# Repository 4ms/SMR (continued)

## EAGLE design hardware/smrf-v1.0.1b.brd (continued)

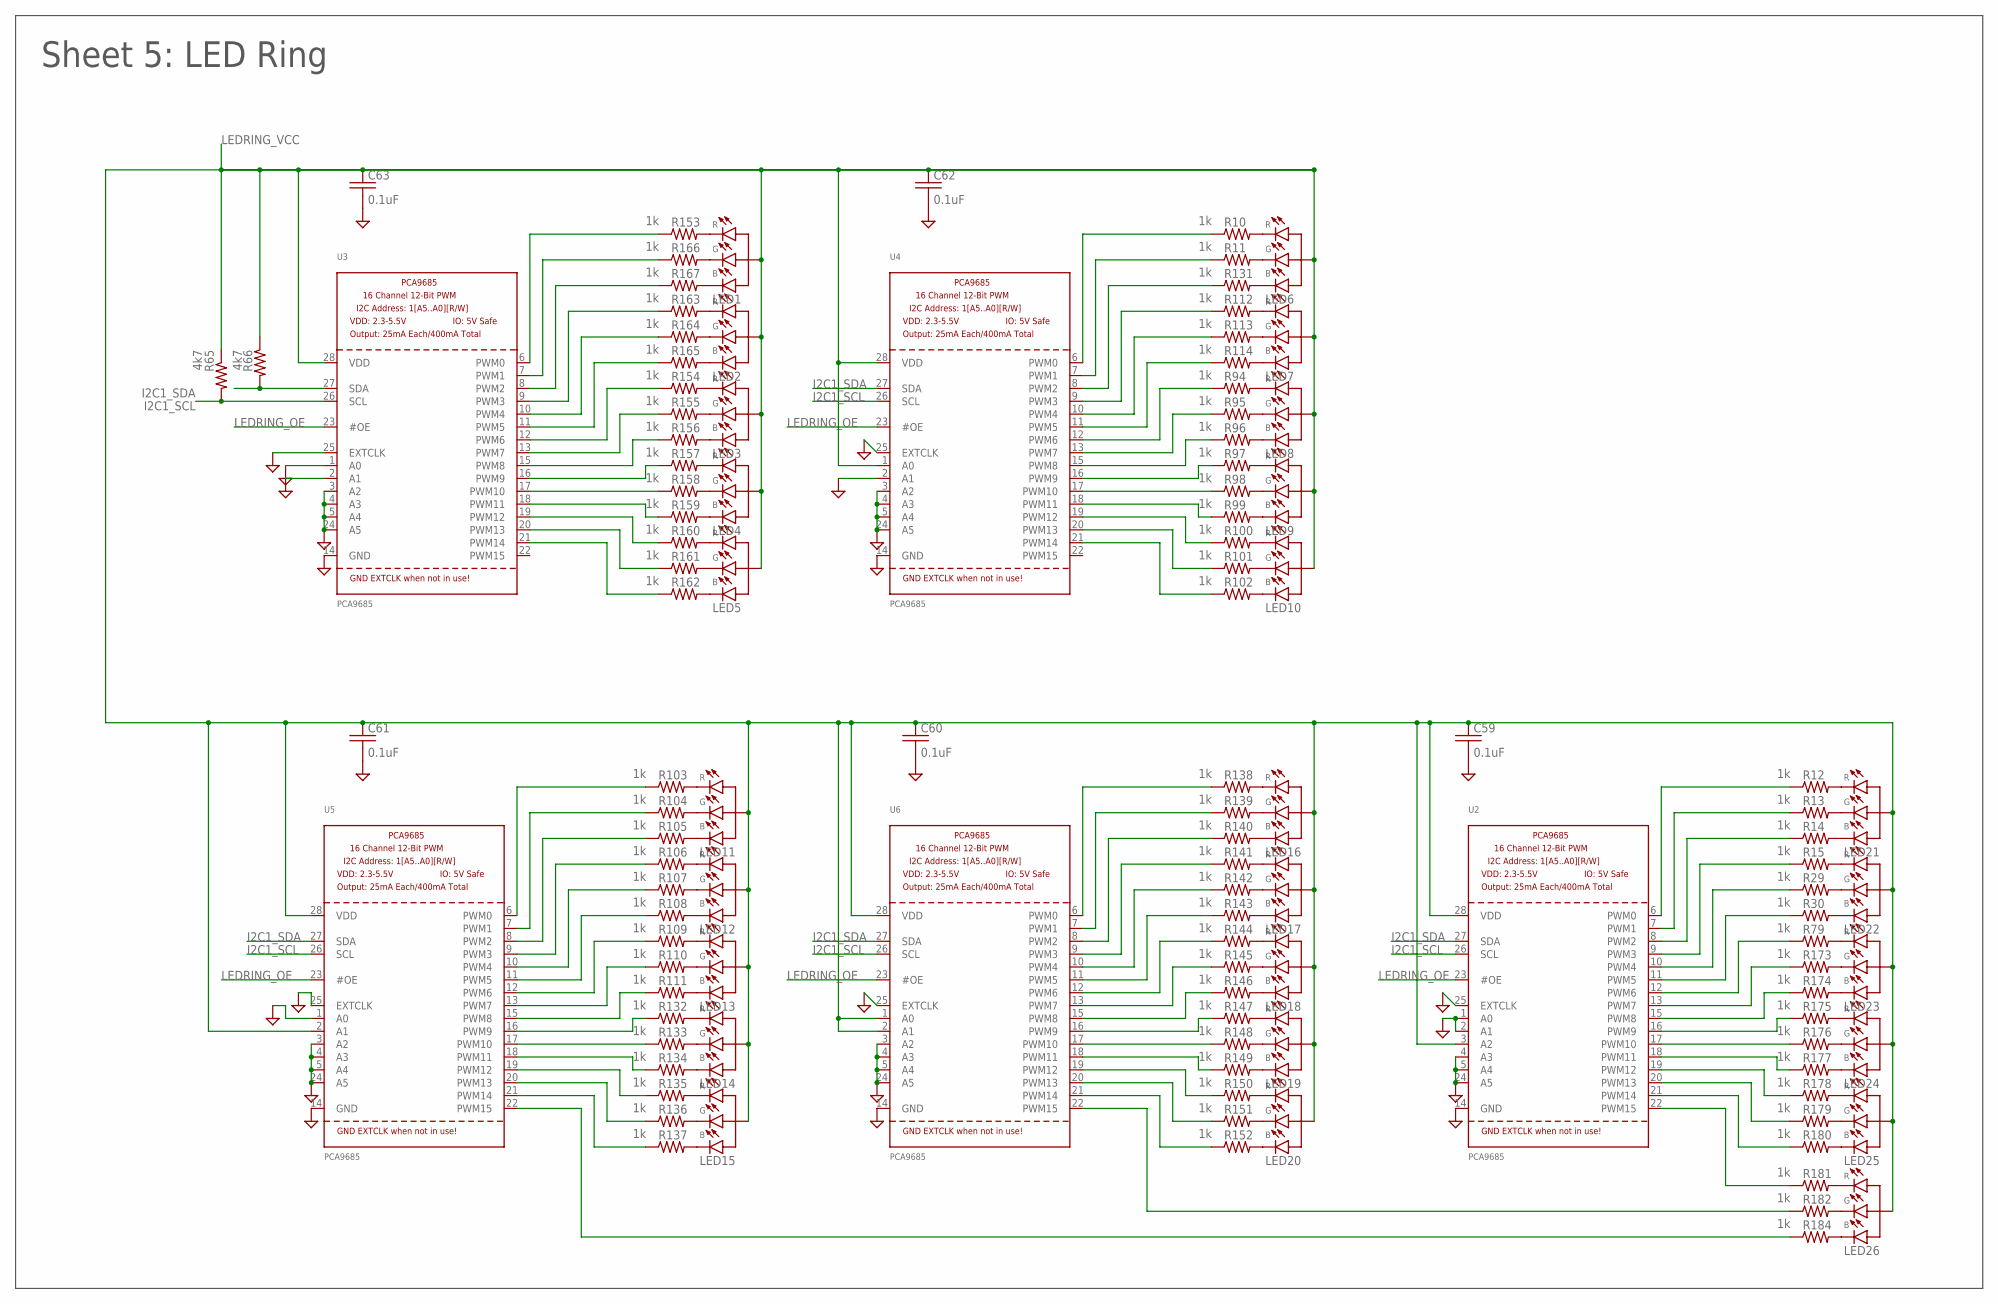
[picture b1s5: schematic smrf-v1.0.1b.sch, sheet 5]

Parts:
C59, C60, C61, C62, C63: 0.1uF; C0603
LED1, LED2, LED3, LED4, LED5, LED6, LED7, LED8, LED9, LED10, LED11, LED12, LED13, LED14, LED15, LED16, LED17, LED18, LED19, LED20, LED21, LED22, LED23, LED24, LED25, LED26: LED-RGB-CA-HEBEI; PLCC4
R10, R11, R12, R13, R14, R15, R29, R30, R79, R94, R95, R96, R97, R98, R99, R100, R101, R102, R103, R104, R105, R106, R107, R108, R109, R110, R111, R112, R113, R114, R131, R132, R133, R134, R135, R136, R137, R138, R139, R140, R141, R142, R143, R144, R145, R146, R147, R148, R149, R150, R151, R152, R153, R154, R155, R156, R157, R158, R159, R160, R161, R162, R163, R164, R165, R166, R167, R173, R174, R175, R176, R177, R178, R179, R180, R181, R182, R184: 1k; R0603
R65, R66: 4k7; R0603
U2, U3, U4, U5, U6: PCA9685; TSSOP28

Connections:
GND: C59.2, C60.2, C61.2, C62.2, C63.2, U2.1 (A0), U2.2 (A1), U2.4 (A3), U2.5 (A4), U2.14 (GND), U2.24 (A5), U2.25 (EXTCLK), U3.1 (A0), U3.2 (A1), U3.3 (A2), U3.4 (A3), U3.5 (A4), U3.14 (GND), U3.24 (A5), U3.25 (EXTCLK), U4.2 (A1), U4.3 (A2), U4.4 (A3), U4.5 (A4), U4.14 (GND), U4.24 (A5), U4.25 (EXTCLK), U5.1 (A0), U5.3 (A2), U5.4 (A3), U5.5 (A4), U5.14 (GND), U5.24 (A5), U5.25 (EXTCLK), U6.3 (A2), U6.4 (A3), U6.5 (A4), U6.14 (GND), U6.24 (A5), U6.25 (EXTCLK); also elsewhere on the board
I2C1_SCL: R65.2, U2.26 (SCL), U3.26 (SCL), U4.26 (SCL), U5.26 (SCL), U6.26 (SCL); also elsewhere on the board
I2C1_SDA: R66.2, U2.27 (SDA), U3.27 (SDA), U4.27 (SDA), U5.27 (SDA), U6.27 (SDA); also elsewhere on the board
LEDRING_OE: U2.23 (#OE), U3.23 (#OE), U4.23 (#OE), U5.23 (#OE), U6.23 (#OE); also elsewhere on the board
LEDRING_VCC: C59.1, C60.1, C61.1, C62.1, C63.1, LED1.P$2 (A), LED2.P$2 (A), LED3.P$2 (A), LED4.P$2 (A), LED5.P$2 (A), LED6.P$2 (A), LED7.P$2 (A), LED8.P$2 (A), LED9.P$2 (A), LED10.P$2 (A), LED11.P$2 (A), LED12.P$2 (A), LED13.P$2 (A), LED14.P$2 (A), LED15.P$2 (A), LED16.P$2 (A), LED17.P$2 (A), LED18.P$2 (A), LED19.P$2 (A), LED20.P$2 (A), LED21.P$2 (A), LED22.P$2 (A), LED23.P$2 (A), LED24.P$2 (A), LED25.P$2 (A), LED26.P$2 (A), R65.1, R66.1, U2.3 (A2), U2.28 (VDD), U3.28 (VDD), U4.1 (A0), U4.28 (VDD), U5.2 (A1), U5.28 (VDD), U6.1 (A0), U6.2 (A1), U6.28 (VDD); also elsewhere on the board
unnamed: LED1.P$1 (CR), R153.2
unnamed: LED1.P$4 (CG), R166.2
unnamed: R12.1, U2.6 (PWM0)
unnamed: R13.1, U2.7 (PWM1)
unnamed: R14.1, U2.8 (PWM2)
unnamed: R15.1, U2.9 (PWM3)
unnamed: LED1.P$3 (CB), R167.2
unnamed: R29.1, U2.10 (PWM4)
unnamed: R30.1, U2.11 (PWM5)
unnamed: LED2.P$1 (CR), R163.2
unnamed: LED2.P$4 (CG), R164.2
unnamed: LED2.P$3 (CB), R165.2
unnamed: LED3.P$1 (CR), R154.2
unnamed: LED3.P$4 (CG), R155.2
unnamed: LED3.P$3 (CB), R156.2
unnamed: LED4.P$1 (CR), R157.2
unnamed: LED4.P$4 (CG), R158.2
unnamed: LED4.P$3 (CB), R159.2
unnamed: R79.1, U2.12 (PWM6)
unnamed: R173.1, U2.13 (PWM7)
unnamed: R174.1, U2.15 (PWM8)
unnamed: LED5.P$1 (CR), R160.2
unnamed: LED5.P$4 (CG), R161.2
unnamed: LED5.P$3 (CB), R162.2
unnamed: LED6.P$1 (CR), R10.2
unnamed: LED6.P$4 (CG), R11.2
unnamed: LED6.P$3 (CB), R131.2
unnamed: LED7.P$1 (CR), R112.2
unnamed: LED7.P$4 (CG), R113.2
unnamed: LED7.P$3 (CB), R114.2
unnamed: LED8.P$1 (CR), R94.2
unnamed: LED8.P$4 (CG), R95.2
unnamed: LED8.P$3 (CB), R96.2
unnamed: LED9.P$1 (CR), R97.2
unnamed: LED9.P$4 (CG), R98.2
unnamed: LED9.P$3 (CB), R99.2
unnamed: LED10.P$1 (CR), R100.2
unnamed: LED10.P$4 (CG), R101.2
unnamed: LED10.P$3 (CB), R102.2
unnamed: LED11.P$1 (CR), R103.2
unnamed: R175.1, U2.16 (PWM9)
unnamed: LED11.P$4 (CG), R104.2
unnamed: LED11.P$3 (CB), R105.2
unnamed: LED12.P$1 (CR), R106.2
unnamed: LED12.P$4 (CG), R107.2
unnamed: LED12.P$3 (CB), R108.2
unnamed: LED13.P$1 (CR), R109.2
unnamed: LED13.P$4 (CG), R110.2
unnamed: LED14.P$1 (CR), R132.2
unnamed: LED14.P$4 (CG), R133.2
unnamed: LED14.P$3 (CB), R134.2
unnamed: LED15.P$1 (CR), R135.2
unnamed: LED15.P$4 (CG), R136.2
unnamed: R176.1, U2.17 (PWM10)
unnamed: R177.1, U2.18 (PWM11)
unnamed: LED15.P$3 (CB), R137.2
unnamed: LED16.P$1 (CR), R138.2
unnamed: LED16.P$4 (CG), R139.2
unnamed: LED16.P$3 (CB), R140.2
unnamed: LED17.P$1 (CR), R141.2
unnamed: LED17.P$4 (CG), R142.2
unnamed: LED17.P$3 (CB), R143.2
unnamed: LED18.P$1 (CR), R144.2
unnamed: LED18.P$4 (CG), R145.2
unnamed: LED18.P$3 (CB), R146.2
unnamed: LED19.P$1 (CR), R147.2
unnamed: LED19.P$4 (CG), R148.2
unnamed: LED19.P$3 (CB), R149.2
unnamed: LED20.P$1 (CR), R150.2
unnamed: LED20.P$4 (CG), R151.2
unnamed: LED20.P$3 (CB), R152.2
unnamed: LED13.P$3 (CB), R111.2
unnamed: R153.1, U3.6 (PWM0)
unnamed: R166.1, U3.7 (PWM1)
unnamed: R167.1, U3.8 (PWM2)
unnamed: R163.1, U3.9 (PWM3)
unnamed: R164.1, U3.10 (PWM4)
unnamed: R165.1, U3.11 (PWM5)
unnamed: R154.1, U3.12 (PWM6)
unnamed: R155.1, U3.13 (PWM7)
unnamed: R156.1, U3.15 (PWM8)
unnamed: R157.1, U3.16 (PWM9)
unnamed: R158.1, U3.17 (PWM10)
unnamed: R159.1, U3.18 (PWM11)
unnamed: R160.1, U3.19 (PWM12)
unnamed: R161.1, U3.20 (PWM13)
unnamed: R162.1, U3.21 (PWM14)
unnamed: R178.1, U2.19 (PWM12)
unnamed: R10.1, U4.6 (PWM0)
unnamed: R11.1, U4.7 (PWM1)
unnamed: R131.1, U4.8 (PWM2)
unnamed: R112.1, U4.9 (PWM3)
unnamed: R113.1, U4.10 (PWM4)
unnamed: R114.1, U4.11 (PWM5)
unnamed: R94.1, U4.12 (PWM6)
unnamed: R95.1, U4.13 (PWM7)
unnamed: R96.1, U4.15 (PWM8)
unnamed: R97.1, U4.16 (PWM9)
unnamed: R98.1, U4.17 (PWM10)
unnamed: R99.1, U4.18 (PWM11)
unnamed: R100.1, U4.19 (PWM12)
unnamed: R101.1, U4.20 (PWM13)
unnamed: R102.1, U4.21 (PWM14)
unnamed: R179.1, U2.20 (PWM13)
unnamed: R103.1, U5.6 (PWM0)
unnamed: R104.1, U5.7 (PWM1)
unnamed: R105.1, U5.8 (PWM2)
unnamed: R106.1, U5.9 (PWM3)
unnamed: R107.1, U5.10 (PWM4)
unnamed: R108.1, U5.11 (PWM5)
unnamed: R109.1, U5.12 (PWM6)
unnamed: R110.1, U5.13 (PWM7)
unnamed: R111.1, U5.15 (PWM8)
unnamed: R132.1, U5.16 (PWM9)
unnamed: R133.1, U5.17 (PWM10)
unnamed: R134.1, U5.18 (PWM11)
unnamed: R135.1, U5.19 (PWM12)
unnamed: R136.1, U5.20 (PWM13)
unnamed: R137.1, U5.21 (PWM14)
unnamed: R180.1, U2.21 (PWM14)
unnamed: LED21.P$1 (CR), R12.2
unnamed: LED21.P$4 (CG), R13.2
unnamed: LED21.P$3 (CB), R14.2
unnamed: LED22.P$1 (CR), R15.2
unnamed: LED22.P$4 (CG), R29.2
unnamed: LED22.P$3 (CB), R30.2
unnamed: LED23.P$1 (CR), R79.2
unnamed: LED23.P$4 (CG), R173.2
unnamed: LED23.P$3 (CB), R174.2
unnamed: LED24.P$1 (CR), R175.2
unnamed: LED24.P$4 (CG), R176.2
unnamed: LED24.P$3 (CB), R177.2
unnamed: R138.1, U6.6 (PWM0)
unnamed: R139.1, U6.7 (PWM1)
unnamed: R140.1, U6.8 (PWM2)
unnamed: R141.1, U6.9 (PWM3)
unnamed: R142.1, U6.10 (PWM4)
unnamed: R143.1, U6.11 (PWM5)
unnamed: R144.1, U6.12 (PWM6)
unnamed: R145.1, U6.13 (PWM7)
unnamed: R146.1, U6.15 (PWM8)
unnamed: R147.1, U6.16 (PWM9)
unnamed: R148.1, U6.17 (PWM10)
unnamed: R149.1, U6.18 (PWM11)
unnamed: R150.1, U6.19 (PWM12)
unnamed: R151.1, U6.20 (PWM13)
unnamed: R152.1, U6.21 (PWM14)
unnamed: LED25.P$1 (CR), R178.2
unnamed: LED25.P$4 (CG), R179.2
unnamed: LED25.P$3 (CB), R180.2
unnamed: LED26.P$1 (CR), R181.2
unnamed: LED26.P$4 (CG), R182.2
unnamed: LED26.P$3 (CB), R184.2
unnamed: R181.1, U2.22 (PWM15)
unnamed: R182.1, U6.22 (PWM15)
unnamed: R184.1, U5.22 (PWM15)

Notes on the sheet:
Sheet 5: LED Ring

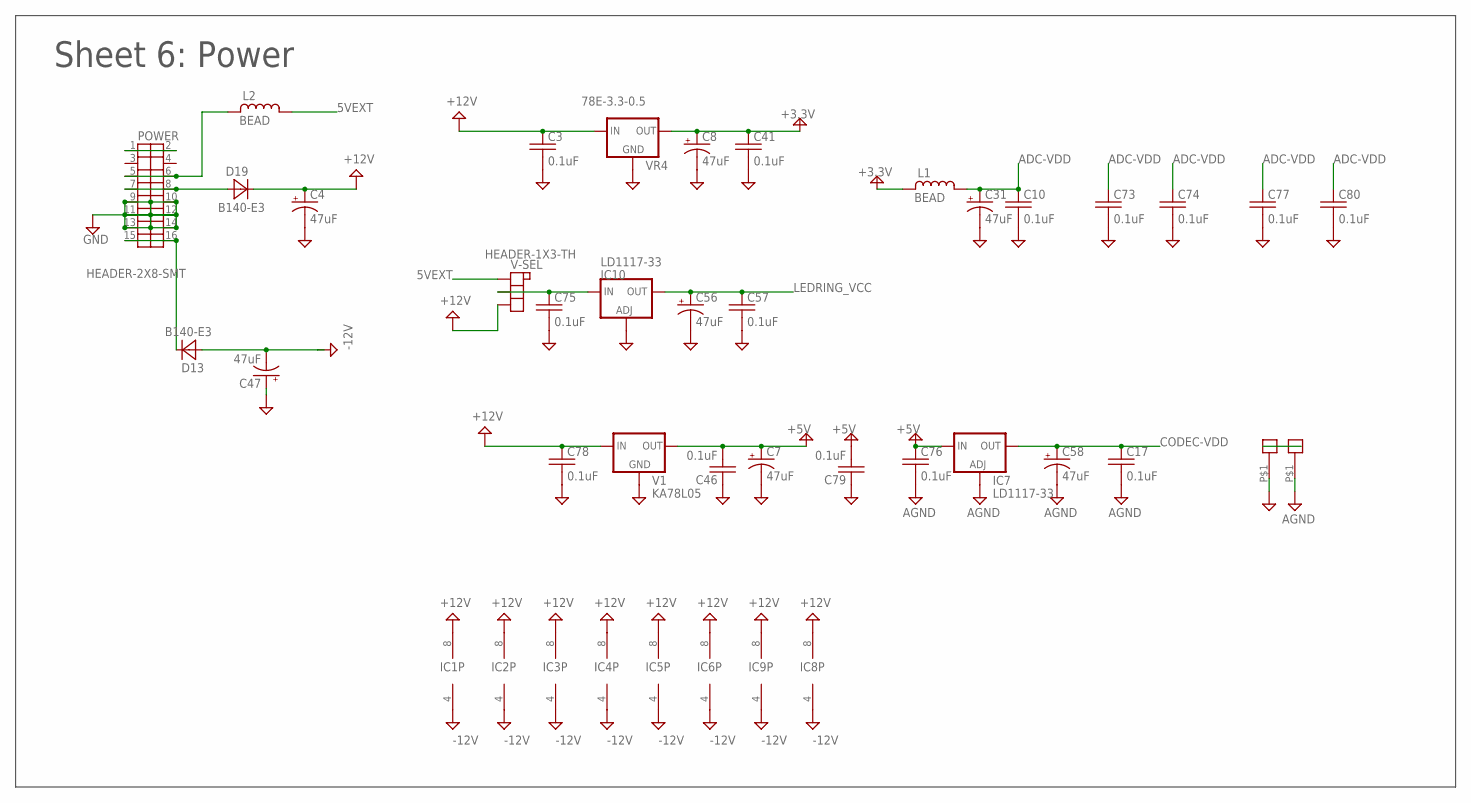
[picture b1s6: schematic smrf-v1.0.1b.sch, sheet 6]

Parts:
AGND: PAD-06
C3, C10, C17, C41, C46, C57, C73, C74, C75, C76, C77, C78, C79, C80: 0.1uF; C0603
C4, C7, C8, C31, C47, C56, C58: 47uF; C-POL-5
D13, D19: B140-E3; SMA
DGND: PAD-06
IC1, IC2, IC3, IC4, IC5, IC6, IC8, IC9: TL082; TSSOP8
IC7, IC10: LD1117-33; SOT223
L1, L2: BEAD; 0603
POWER: HEADER-2X8-SMT; HEADER-2X8-SMT-SHROUDED
V1: KA78L05; SOT89
V-SEL: HEADER-1X3-TH
VR4: 78E-3.3-0.5; RECOM-DCDC

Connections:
5VEXT: L2.2 (4), V-SEL.P$1
+3.3V: C8.+, C41.1, L1.1, VR4.P$3 (OUT); also elsewhere on the board
+5V: C7.+, C46.2, C76.1, C79.2, IC7.3 (IN), V1.1 (OUT); also elsewhere on the board
+12V: C3.1, C4.+, C78.1, D19.K (C), IC1.8 (V+), IC2.8 (V+), IC3.8 (V+), IC4.8 (V+), IC5.8 (V+), IC6.8 (V+), IC8.8 (V+), IC9.8 (V+), V1.3 (IN), V-SEL.P$3, VR4.P$1 (IN)
-12V: C47.-, D13.A, IC1.4 (V-), IC2.4 (V-), IC3.4 (V-), IC4.4 (V-), IC5.4 (V-), IC6.4 (V-), IC8.4 (V-), IC9.4 (V-)
ADC-VDD: C10.1, C31.+, C73.1, C74.1, C77.1, C80.1, L1.2 (4); also elsewhere on the board
AGND: AGND.P$1, C17.2, C58.-, C76.2, IC7.1 (ADJ); also elsewhere on the board
CODEC-VDD: C17.1, C58.+, IC7.2 (OUT), IC7.4 (OUT); also elsewhere on the board
GND: C3.2, C4.-, C7.-, C8.-, C10.2, C31.-, C41.2, C46.1, C47.+, C56.-, C57.2, C73.2, C74.2, C75.2, C77.2, C78.2, C79.1, C80.2, DGND.P$1, IC10.1 (ADJ), POWER.9, POWER.10, POWER.11, POWER.12, POWER.13, POWER.14, V1.2A (GND), V1.2B (GND), VR4.P$2 (GND); also elsewhere on the board
LEDRING_VCC: C56.+, C57.1, IC10.2 (OUT), IC10.4 (OUT); also elsewhere on the board
unnamed: C75.1, IC10.3 (IN), V-SEL.P$2
unnamed: L2.1, POWER.5, POWER.6
unnamed: D19.A, POWER.7, POWER.8
unnamed: D13.K (C), POWER.15, POWER.16
unnamed: POWER.1, POWER.2

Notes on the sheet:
Sheet 6: Power

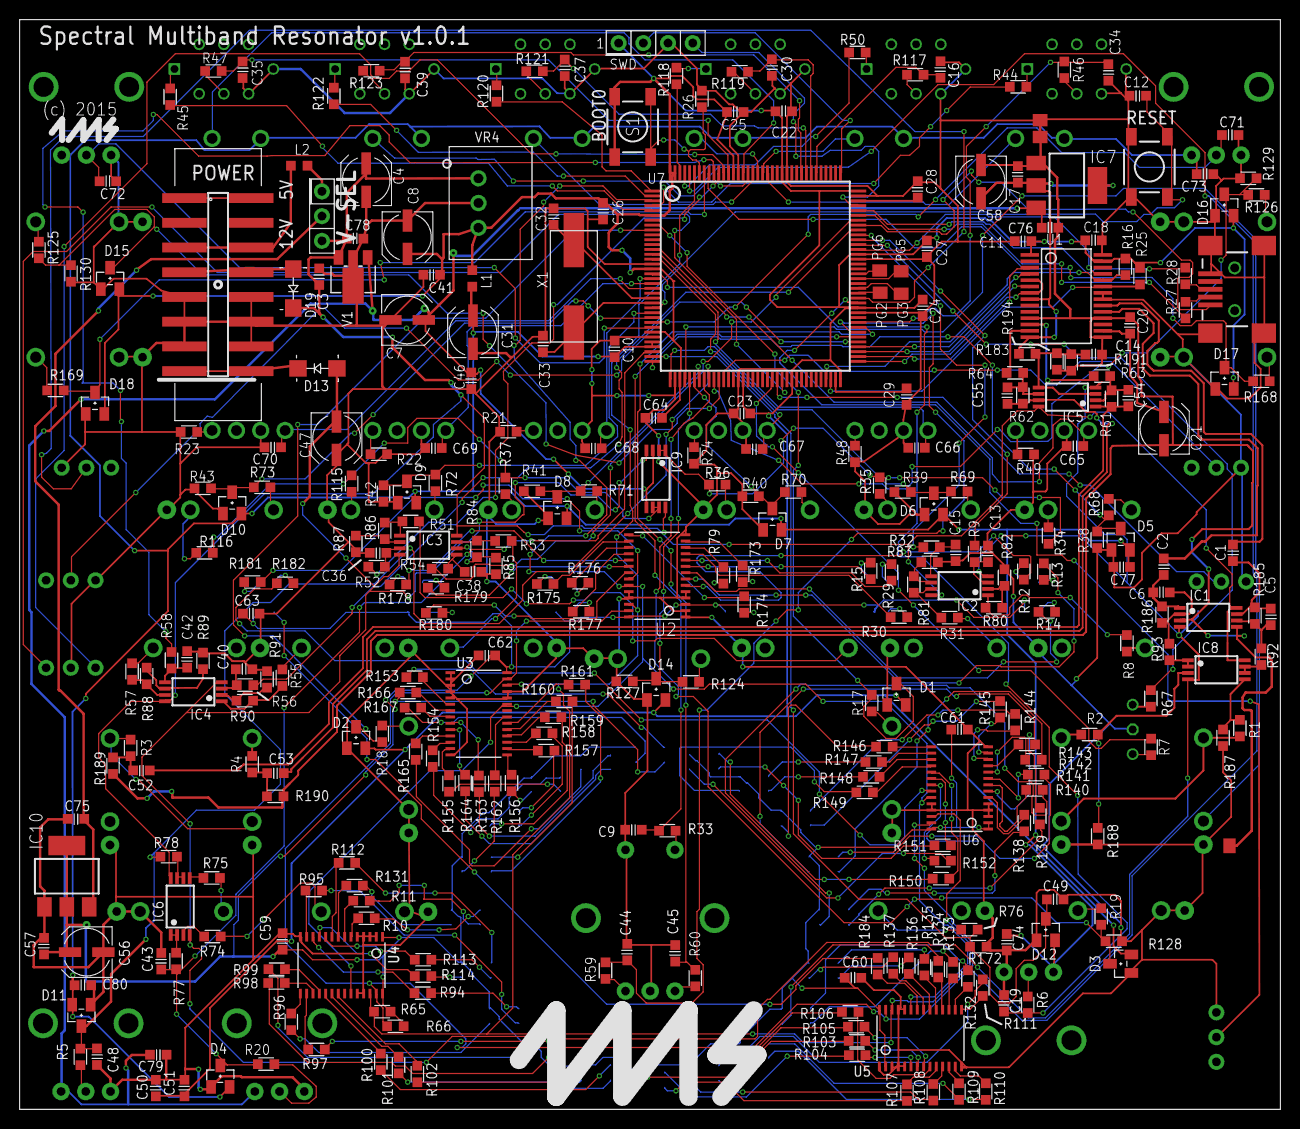
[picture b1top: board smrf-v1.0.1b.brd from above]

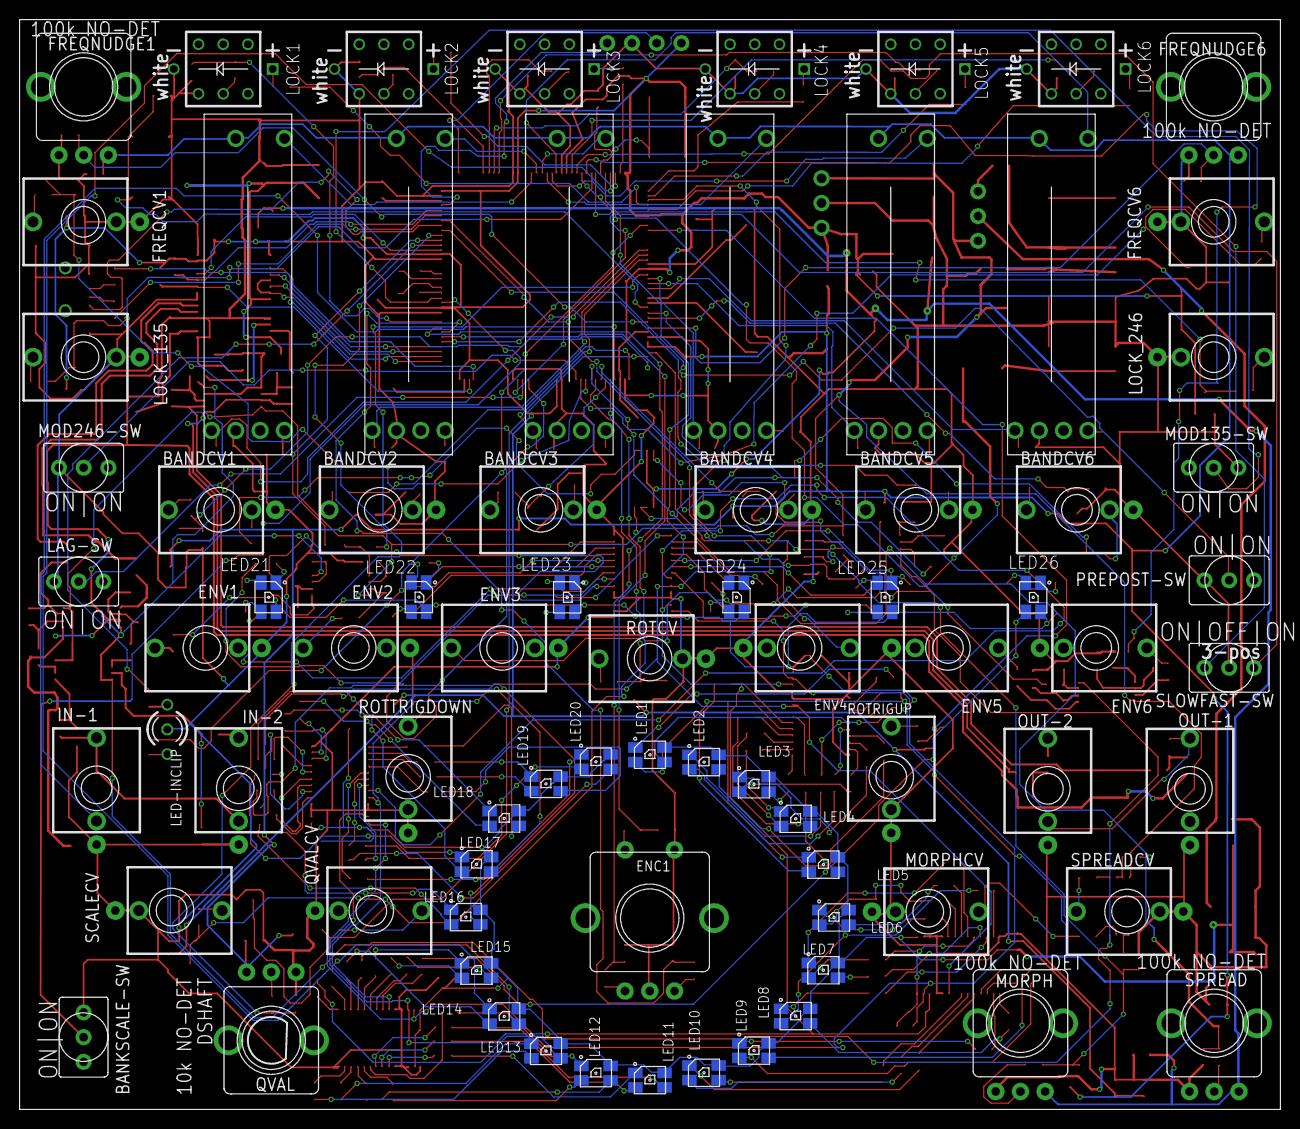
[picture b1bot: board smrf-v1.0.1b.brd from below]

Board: 2 copper layers, 129.5 x 112.0 mm, 402 parts (78 on the bottom side), 364 nets.

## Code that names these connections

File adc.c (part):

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	GPIO_Init(GPIOF, &GPIO_InitStructure);

	/* ADC1 regular channel configuration -----------------------------------*/ 
	ADC_RegularChannelConfig(ADC1, ADC_Channel_0, MORPH_ADC+1, ADC_SampleTime_144Cycles); //[0]: PA0, Morph
	ADC_RegularChannelConfig(ADC1, ADC_Channel_1, QVAL_ADC+1, ADC_SampleTime_144Cycles); //[1]: PA1, Q CV
	ADC_RegularChannelConfig(ADC1, ADC_Channel_2, LEVEL_ADC_BASE+1, ADC_SampleTime_144Cycles); //[2]: PA2: filter 1
	ADC_RegularChannelConfig(ADC1, ADC_Channel_3, LEVEL_ADC_BASE+2, ADC_SampleTime_144Cycles); //[3]: PA3: filter 2
	ADC_RegularChannelConfig(ADC1, ADC_Channel_6, LEVEL_ADC_BASE+3, ADC_SampleTime_144Cycles); //[4]: PA6: filter 3
	ADC_RegularChannelConfig(ADC1, ADC_Channel_7, LEVEL_ADC_BASE+4, ADC_SampleTime_144Cycles); //[5]: PA7: filter 4
	ADC_RegularChannelConfig(ADC1, ADC_Channel_10, LEVEL_ADC_BASE+5, ADC_SampleTime_144Cycles); //[6]: PC0: filter 5
	ADC_RegularChannelConfig(ADC1, ADC_Channel_11, LEVEL_ADC_BASE+6, ADC_SampleTime_144Cycles); //[7]: PC1: filter 6
	ADC_RegularChannelConfig(ADC1, ADC_Channel_12, FREQNUDGE1_ADC+1, ADC_SampleTime_144Cycles); //[8]: PC2: freq 1
	ADC_RegularChannelConfig(ADC1, ADC_Channel_13, FREQNUDGE6_ADC+1, ADC_SampleTime_144Cycles);//[9]: PC3: freq 6
	ADC_RegularChannelConfig(ADC1, ADC_Channel_14, SCALE_ADC+1, ADC_SampleTime_144Cycles); //[10]: PC4: Scale CV
	ADC_RegularChannelConfig(ADC1, ADC_Channel_15, SPREAD_ADC+1, ADC_SampleTime_144Cycles); //[11]: PC5: spread CV
	ADC_RegularChannelConfig(ADC1, ADC_Channel_5, ROTCV_ADC+1, ADC_SampleTime_144Cycles);//[12]: PA5: Rot CV/Reset
	ADC_RegularChannelConfig(ADC1, ADC_Channel_8, FREQCV1_ADC+1, ADC_SampleTime_144Cycles);//[13]: PB0: FM_135
	ADC_RegularChannelConfig(ADC1, ADC_Channel_9, FREQCV6_ADC+1, ADC_SampleTime_144Cycles);//[14]: PB1: FM_246

	DMA_ITConfig(DMA2_Stream0, DMA_IT_TC, DISABLE);
	
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	GPIO_Init(GPIOF, &GPIO_InitStructure);

	/* ADC3 regular channel configuration -----------------------------------*/
	ADC_RegularChannelConfig(ADC3, ADC_Channel_4, 1, ADC_SampleTime_480Cycles); //[0]: PF6: Q POT
	ADC_RegularChannelConfig(ADC3, ADC_Channel_9, 2, ADC_SampleTime_480Cycles); //[1]: PF3: Slider 1
	ADC_RegularChannelConfig(ADC3, ADC_Channel_14, 3, ADC_SampleTime_480Cycles); //[2]: PF4: Slider 2
	ADC_RegularChannelConfig(ADC3, ADC_Channel_15, 4, ADC_SampleTime_480Cycles); //[3]: PF5: Slider 3
	ADC_RegularChannelConfig(ADC3, ADC_Channel_5, 5, ADC_SampleTime_480Cycles); //[4]: PF7: Slider 4
	ADC_RegularChannelConfig(ADC3, ADC_Channel_6, 6, ADC_SampleTime_480Cycles); //[5]: PF8: Slider 5
	ADC_RegularChannelConfig(ADC3, ADC_Channel_7, 7, ADC_SampleTime_480Cycles); //[6]: PF9: Slider 6

	DMA_ITConfig(DMA2_Stream1, DMA_IT_TC, DISABLE);

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
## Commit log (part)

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2015-02-19 Initial commit -- added GAMMA_SPREAD1, bank/scale changing using just rotary (no flip switch), envelope speed switch, variable Q, and changed LAG controls to just a single on/off flip switch
2015-03-25 Proto version 5 (lock buttons, Q knob, Scale rotation switch, 3-pos Env speed, CV slew grabs morph timing, Lock jacks, Freq CV, mod246/mod135 switches)
2015-04-06 New colors, better fading of LEDs in rotate morph, better handling of spread and rotate, new display for scale mode. Spread now crosses scales within a bank
2015-07-02 testing maxq...
2015-08-08 Distribution v1.0.1
2015-09-01 cleaned up comments
2015-09-04 Directory structure changes, cleaned up comments, cleaned up license notices
2015-09-04 Added LICENSE file
2015-09-04 updated make wav to existing directory structure
2015-09-04 no builds
2015-09-04 fixed path to main.elf
2015-09-04 Added instructions for setting up environment in README
2015-09-04 typo in README
2015-09-06 README instructions clarified, moved main.map to build dir
2015-09-11 Added schematic (PDF)
2015-09-24 EAGLE board and schematics added
2015-10-03 Longer -k blank duration time for fsk-wave file
2015-10-03 1V per octave was at 1.5V per octave, changed to 1.0V. Added firmware version display in change scale mode
2015-10-22 added CHANGELOG
2015-10-22 renamed CHANGELOG
2015-11-12 Reference to source of dsp filter
2015-11-12 Updated CHANGELOG to version 2 revision 2
2015-12-19 Tracking can be adjusted in system mode, fixed bug with led_ring display while editting color scheme
2015-12-19 Updated changelog to v3
2015-12-21 LED ring fix in EDITCOLORS
2015-12-22 Custom color scheme LED ring RGB value overflow fix
2015-12-31 Added ability to compensate tracking independently on evens and odds
2016-01-19 Volt Octave output on ENV OUT jacks -- only semitones
2016-03-04 README update
2016-04-19 Updated LICENSE to reflect hardware
2016-10-04 first stable iteration of two-pass filter for team-testing in showroom
2016-10-05 nudge_udate's clean slate
2016-10-06 HAPPY ACCIDENT MUTE BUTTONS -> TUNABLE OFFSET KEYBOARD
2016-10-06 [freq nudge knob -> -semitone/+semitone] && [ {[freq nudge knob]+[mute]} -> 12-quantized-semitones coearse adjustemnt]
2016-10-06 coarse tune maintains lock buttons
2016-10-07 [fine nudge never applies to coarse nudge] + [coarse tune available when locked]
2016-10-07 features for freq nudge update are in place. code cleanup pending
2016-10-11 added 6-button coarse tune clear || switched fine tune to 0-1 semitone || switched coarse tune to -6/+6 semitones || freq knob output is 0 at module startup and sleeps until knob is rotated by at lea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
2016-10-13 fine tune pink:blue visual feedback when tuning || lock button press displays current fine tune status || optimized visualization release times based on use: tuning odds and even separately or togeth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
2016-10-13 135 and 246 switch states shown on fine tune env led diplays w/ blinking || fixed typo on toggle part
2016-10-13 channels that are lock switched show as blinking on fine tune display || switching 135/246 switches display corresponding fine tunes || added display release time when fine tune is looked at by press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
2016-10-18 added major scale bank with major scale, major pentatonic, and various major chords - all in equal temperament
2016-10-19 added najor and minor scales. FIXME: number of banks currently limited to 16 || started coding binary display when choosing scale banks
2016-10-19 scale selection made easier using envled || banks are now gathered by groups of 6 || envled shows bank colors for current group || burrent bank position within group blinks on envleds || scale colors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
2016-10-20 Changed fine tune colors to white/blue
2016-10-20 Freq nudge indicator lights are dimmed when disabled (instead flashing)
2016-10-20 NUMSCALEBANKS > 16 now available
2016-10-20 Fine tune LEDs blink a few times when changing states. Fixed bug with fine tune display disabled after coarse tuning
2016-10-20 Fixed flicker when unlocking
2016-10-21 Much improved tracking using floats, but very CPU intensive
2016-10-21 optimized crossfade and q ranges || FIXME: put crossfade point further. Separately , keep end q point for second filter but change its start point for more range || UPDATE QVAL LOWPASS LESS OFTEN TO 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
2016-10-21 optimized with uint32_t instead of floats in comparisons
2016-10-22 Added note in main.c about timing measurements of the main loop
2016-10-23 Tracks FM in the Freq jack better: Added an update timer to run the param_read_freq_nudge() function and renamed it param_read_freq(). Running it on an interrupt is essential for tracking the CV jack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
2016-10-23 Fixed bug where channels 2 and 4 would not be tuned on boot (thus in VOCT mode their LEDs were off). Changed the way ENV LEDs display in VOCT mode so that they don't go all the way off. Cleaned up so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
2016-10-23 Comments in main.c
2016-10-24 optimized Qval LPF to leave more cpu headroom. cleaned up code
2016-10-24 found phase cancellation in filters crossfade and fixed it by inverting phase of filter 2
2016-10-24 optimized crossfade and Q coefficients to take advantage of full range of both one pass and two pass
2016-10-25 filter mode gets canged in system mode, 1 round trip knob turn on freqnudge1 || filter type gets canged on 1 round trip knob turn on freqnudge6|| FIXME cpu choking || code cleanup, removed all testin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
2016-10-26 fixed cpu chocking || made swithcing filter types and modes easier
2016-10-26 filter mode gets saved/recalled in SRAM/FLASH || improved consistency on filter mode/style switching
2016-10-26 two pass merged into devmaster kept separate until debugging complete
2016-10-31 added param functions to read channel level and Q adc readouts one at a time. Code compiles and run. Initial commit is functional
2016-10-31 fixed 6kHz on volume slider by updating volume readout before every use. No change in how it is used. FIXME: Noticed morphing has this feature too. Tried updating motion_morphpos more often for each 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
2016-10-31 morph slightly choking cpu is seen on initial twopass branch. Moving on to takling 6kHz on Q before adressing that
2016-10-31 starting point before applying the same strategy to q readout
2016-10-31 grabbed Makefile from dev_twopass_noisetest
2016-11-01 updated the minimum cvlag to a higher value. Added LPF to volume slider ADC readout prior to it being comined with the CV ins. LEVEL FIXED
2016-11-01 end of the day, Tried multiple angles of attack on Qval noise. Thought I had foud something with floating point error at last. Didn't seem to have fixed it though.
2016-11-01 lowered qnoise to acceptable level. Improved crossfade. CPU is choking, mostly on rotation when morph is on, less on spread. FIXME: freeup cpu headroom
2016-11-01 cleaned up code. FIXME: Need to assess CPU choking
2016-11-02 Hold down ROTATE while flipping to FAST to enable VOCT output mode
2016-11-03 current code optimization, more to come
2016-11-03 fixed j/i swap in filter.c, where the channel_level code was pasted in
2016-11-03 pulled param_read_q out of the channel loop, put in lots of debug flags to measure timing
2016-11-03 save freq blocks in binary. Display freq blocks on LED ring with dark white. Clear freq blocks with 6x lock press + ROTARY_SW. scale and system mode access with ROTARY_SW disabled when any lock is pr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
2016-11-03 enabled clearing freq blocks one at a time
2016-11-03 Messed it up
2016-11-04 fixed spread so it doesnt crash and so it avoids blocked freq
2016-11-04 Moved param_read_q() to inside the inner loop to attempt to read it faster and get rid of the 6kHz update noise. It's still there, but improved. Also added it to the non TWOPASS filter.c sections. Go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
2016-11-04 Moved param_update_q() outside the channel loop and the noise is the same. filter.c takes 92us/122us
2016-11-04 added limit to number of blocks that can be applied. FIXME: block number limit is not applying properly || rotating with knob doesn't avoid blocks - or does but keep morph between positions || get th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
2016-11-04 intermediate commit to switch branches and check feature on rotate CV jack
2016-11-04 freq block implemented and working for rotate, rotate CW, rotate CCW, spread and corresponding CV. NOTE: rotate CV works forward but never crosses locks or blocks backwards. Also the case on original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
2016-11-04 Added a BASE_TRACKOFFSET to counter inevitable small positive voltage on the Freq jacks. This addresses the bug where freq_shift[2] would be 1.03 with nothing plugged in the jack and then drop to 1.0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
2016-11-04 Fixed bug where freq_nudge had no effect on one-pass MAXQ mode
2016-11-04 fixed inconsistent response quen trying to freq block \/ un-block
2016-11-04 fixed limit on number of freq blocked. now working and limited to 14
2016-11-04 first installement of freqblock save/load. Works with SRAM deosn't work with FLASH
2016-11-07 scales reordered. Started working on new scale display - by category - neeeds more work. Will pursue later
2016-11-07 updated scale order by category: equal temperament, just intonation, civilisations and world, exotic, user scales
2016-11-07 scale banks displayed by group (color) on ENV LED and LED RING
2016-11-07 moved buchla EQ into modern scales group. Limited to 1 user scale bank
2016-11-08 fixed change of pitch when switching filter types. Pitch maintained, even with coarse tuning on
2016-11-08 added name and contact to files changed
2016-11-08 BPRE fully fixed
2016-11-08 added comments to part that could be improved
2016-11-08 Changed TWOPASS and ONEPASS to non-zero values, so that we can force TWOPASS for legacy slots in user flash. Also forcing ONEPASS if we read a legacy slot as BPRE.
2016-11-09 Changed version number to 5
2016-11-09 re-ordered scales in both major and minor scale banks
2016-11-09 Fixed DIATONIC scale notes, and added equal temp version. Also simplified the scale bank lookup in filter.c.
2016-11-09 added timer to scale bank ENV LED display
2016-11-09 Re-ordered Gamelan scales. Fixed bug where two banks in BPRE would not load because c_loq was not set for them
2016-11-10 disabled fine tune display on BPRE - did the same for coarse tune, as an extra precaution
2016-11-14 fixed erratic audio output when q-locking channel
2016-11-14 divided range of cv slew by two
2016-11-15 added equal temperament one-interval and two-interval scales. Fixed typos in just intonation versions of these scales. Updated scale LED display accordingly
2016-11-20 calibrated two pass filter output. Created a calibration lookup table. Two pass filter output is now constant throughout vaues of qval. Adjusted crossfade point and second filter gain. No more dip in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
2016-11-20 cleaned up code. Removed old comments and some unsed variables. Tested the new two-pass swell with maximum q and made shure it still works with gain adjustment - just in case
2016-11-21 cleaned up filter.c. Removed un-used variables and related code. Simplified and gathered operations. Moved global variables to local as much as possible so they are less likely to be stored in RAM.
2016-11-21 fixed click when morphing. there was a typo in the filter output calculation when morphing
2016-11-22 applied adjustment gain to PWM output when in 1Voct so that C2 = 1V, vs A1=1V before. Also made small adjustments to C2 is closer to 1.0V, versus 1.16V before.
2016-11-22 tuned 1voct pwm out so output voltage for octaves of C are closer to integer values
2016-11-23 Prevented ENVOUT_PWM from going negative, and adjusted the adjustment so that C1 is 1.012V (C2 is 0.012V)
2016-11-29 Shortened trigger length and recovery time from 2000 to 285 which is about 100ms. Also added feature where the channel_level[] is cached into stored_trigger_level[] if we're in trigger mode and the s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
2016-11-29 fixed freeze bug when 14 highest notes are forbidden and SMR is receiving rotate CV, spread CV and evens nudge CV
2016-12-05 Updated CHANGELOG
2017-02-16 Added settings folder
2017-02-16 Added Eclipse project files
2017-02-21 Removed F7 changes, should be a working F4 version that compiles with latest GCC
2017-02-21 Working: Release candidate for code that compiles on latest GCC
2017-03-29 ignoring sublime workspace
2018-01-02 Fixed bug where qval[] loaded from slots got overridden immediately
    Also added section in Makefile to allow for compiling a single file with -O0
2018-01-02 Formatting cleanup and project file removal
2019-01-22 Applied contemplation mode patch (second revision) from Jon Butler
2019-04-01 Testing Mode for kit PCBs
2019-04-01 TESTING_MODE created for testing Kit PCBs
2020-08-25 Full init of PWM outputs
    fixes issue with env out jacks 3/4 sometimes not outputting
